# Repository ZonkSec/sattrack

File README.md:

# SatTrack
DIY Satellite Tracker for Ham Radio
* For [Arrow II Sat Antenna](https://www.arrowantennas.com/arrowii/146-437.html)
* improved 3D printed parts | [original design by jbyrns](https://www.thingiverse.com/thing:4664558)
* Nema 17 Motors
* on-board tracking software and battery
  * doubles as a counter weight; fewer wires to get tangled 
  * rasperby pi zero
  * custom pcb for:
    * A4988 Stepper Drivers
    * Power regulation
    * Buzzer output
    * Easy connectivity for switches and connections
  * full featured web interface
  * satellite definitions compatible with opengd77
 
 ## Repo Structure
 The repo is broken into several categories:
 * [3d models](3d%20models) - this contains all the 3d parts, as well as hardware needed
 * [app](app) - this contains the python application
 * [hardware](hardware) - this contains the custom pcb

Each category contains it's own readme.md with more details.

 ## Images

<div align="center">

</div>

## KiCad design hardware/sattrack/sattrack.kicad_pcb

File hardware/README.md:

# Hardware

## Parts Needed:
* 1x Custom PCB
* 1x Raspberry Pi Zero W 1 or 2 (other RPis may work, but these are the only I've tested)
* 2x A4988 Stepper Drivers
* 2x "3d pritner" motor wires (depends on your motor, but mine was the standard 4pin XH 2.54 <-> 6pin PH 2.0)
* 2x Nema 17 Stepper Motors
* 1x 100 µF capacitor (C1)
* 1x 330 µF capacitor (C2)
* 1x 1N5819 Diode (D1)
* 1x 330 µH inductor (L1)
* 1x LM2575 5v switching reg (U1)
* 1x Passive Buzzer (BZ1)
* 2x Mini Toggle Switches ([Link](https://www.amazon.com/dp/B0799LBFNY?))
* 3x JST-XH 2.5pitch 2pin parts for motor enable switch, on/off switch, EL endspot microswitch
* 2x JST-XH 2.5pitch 4pin parts for motor connectors
* 1x Micro Limit Switch KW12-3 for EL limit switch
* 1x Battery connector and wires (I used XT60)
* 1x LiPo Battery ([Link to what I use](https://www.amazon.com/gp/product/B0D59XCQ3Z))
* 1x Roll of 1/2in Hook & Loop Straps to strap battery on
* 1x RC Battery Alarm to monitor voltage

<div align="center">

</div>

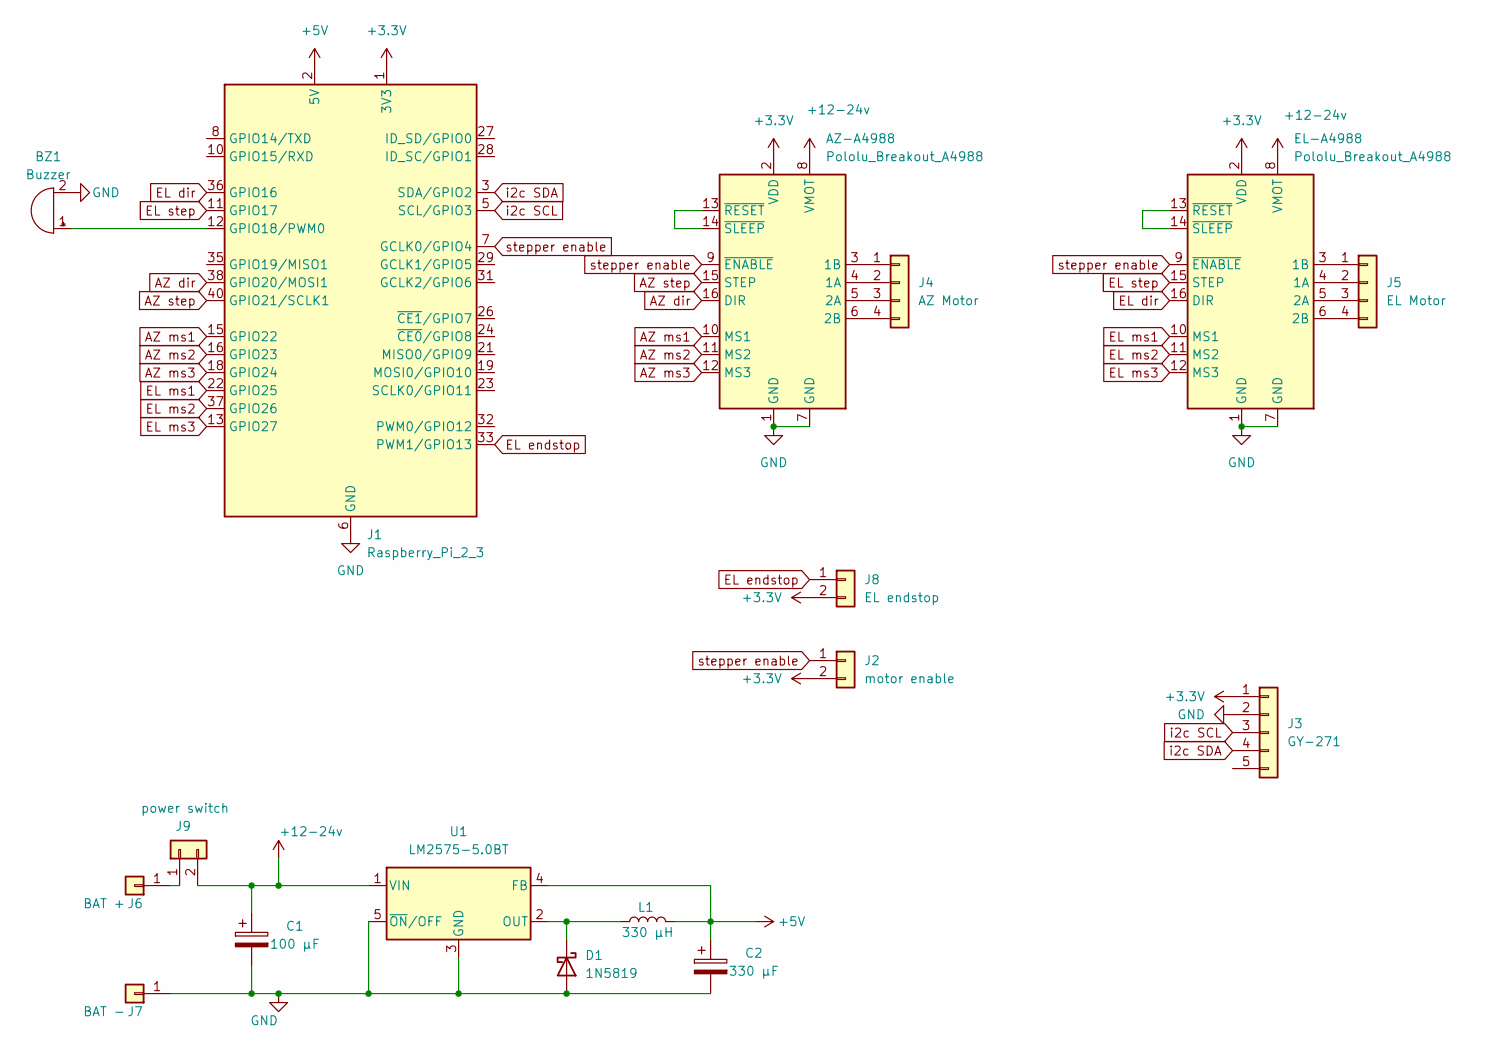
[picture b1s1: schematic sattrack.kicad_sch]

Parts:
AZ-A4988: Pololu_Breakout_A4988; Pololu_Breakout-16_15.2x20.3mm
BZ1: Buzzer; Buzzer_12x9.5RM7.6
C1: 100 µF; CP_Radial_D5.0mm_P2.50mm
C2: 330 µF; CP_Radial_D8.0mm_P3.80mm
D1: 1N5819; D_DO-41_SOD81_P10.16mm_Horizontal
EL-A4988: Pololu_Breakout_A4988; Pololu_Breakout-16_15.2x20.3mm
J1: Raspberry_Pi_2_3; PinHeader_2x20_P2.54mm_Vertical
J2: motor enable; JST_XH_B2B-XH-AM_1x02_P2.50mm_Vertical
J3: GY-271; PinHeader_1x05_P2.54mm_Vertical
J4: AZ Motor; JST_XH_B4B-XH-AM_1x04_P2.50mm_Vertical
J5: EL Motor; JST_XH_B4B-XH-AM_1x04_P2.50mm_Vertical
J6: BAT +; SolderWirePad_1x01_SMD_5x10mm
J7: BAT -; SolderWirePad_1x01_SMD_5x10mm
J8: EL endstop; JST_XH_B2B-XH-AM_1x02_P2.50mm_Vertical
J9: power switch; JST_XH_B2B-XH-AM_1x02_P2.50mm_Vertical
L1: 330 µH; L_Radial_D6.0mm_P4.00mm
U1: LM2575-5.0BT; TO-220-5_Vertical

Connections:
+3.3V: AZ-A4988.2 (VDD), EL-A4988.2 (VDD), J1.1 (3V3), J1.17 (3V3), J2.2, J3.1, J8.2
+5V: C2.1, J1.2 (5V), J1.4 (5V), L1.2, U1.4 (FB)
+12-24v: AZ-A4988.8 (VMOT), C1.1, EL-A4988.8 (VMOT), J9.2, U1.1 (VIN)
AZ dir: AZ-A4988.16 (DIR), J1.38 (GPIO20/MOSI1)
AZ ms1: AZ-A4988.10 (MS1), J1.15 (GPIO22)
AZ ms2: AZ-A4988.11 (MS2), J1.16 (GPIO23)
AZ ms3: AZ-A4988.12 (MS3), J1.18 (GPIO24)
AZ step: AZ-A4988.15 (STEP), J1.40 (GPIO21/SCLK1)
EL dir: EL-A4988.16 (DIR), J1.36 (GPIO16)
EL endstop: J1.33 (PWM1/GPIO13), J8.1
EL ms1: EL-A4988.10 (MS1), J1.22 (GPIO25)
EL ms2: EL-A4988.11 (MS2), J1.37 (GPIO26)
EL ms3: EL-A4988.12 (MS3), J1.13 (GPIO27)
EL step: EL-A4988.15 (STEP), J1.11 (GPIO17)
GND: AZ-A4988.1 (GND), AZ-A4988.7 (GND), BZ1.2 (-), C1.2, C2.2, D1.2 (A), EL-A4988.1 (GND), EL-A4988.7 (GND), J1.6 (GND), J1.9 (GND), J1.14 (GND), J1.20 (GND), J1.25 (GND), J1.30 (GND), J1.34 (GND), J1.39 (GND), J3.2, J7.1, U1.3 (GND), U1.5 (~ON/OFF)
unnamed: AZ-A4988.4 (1A), J4.2
unnamed: AZ-A4988.3 (1B), J4.1
unnamed: AZ-A4988.5 (2A), J4.3
unnamed: AZ-A4988.6 (2B), J4.4
unnamed: AZ-A4988.13 (~RESET), AZ-A4988.14 (~SLEEP)
unnamed: BZ1.1 (+), J1.12 (GPIO18/PWM0)
unnamed: D1.1 (K), L1.1, U1.2 (OUT)
unnamed: EL-A4988.4 (1A), J5.2
unnamed: EL-A4988.3 (1B), J5.1
unnamed: EL-A4988.5 (2A), J5.3
unnamed: EL-A4988.6 (2B), J5.4
unnamed: EL-A4988.13 (~RESET), EL-A4988.14 (~SLEEP)
unnamed: J6.1, J9.1
i2c SCL: J1.5 (SCL/GPIO3), J3.3
i2c SDA: J1.3 (SDA/GPIO2), J3.4
stepper enable: AZ-A4988.9 (~ENABLE), EL-A4988.9 (~ENABLE), J1.7 (GCLK0/GPIO4), J2.1

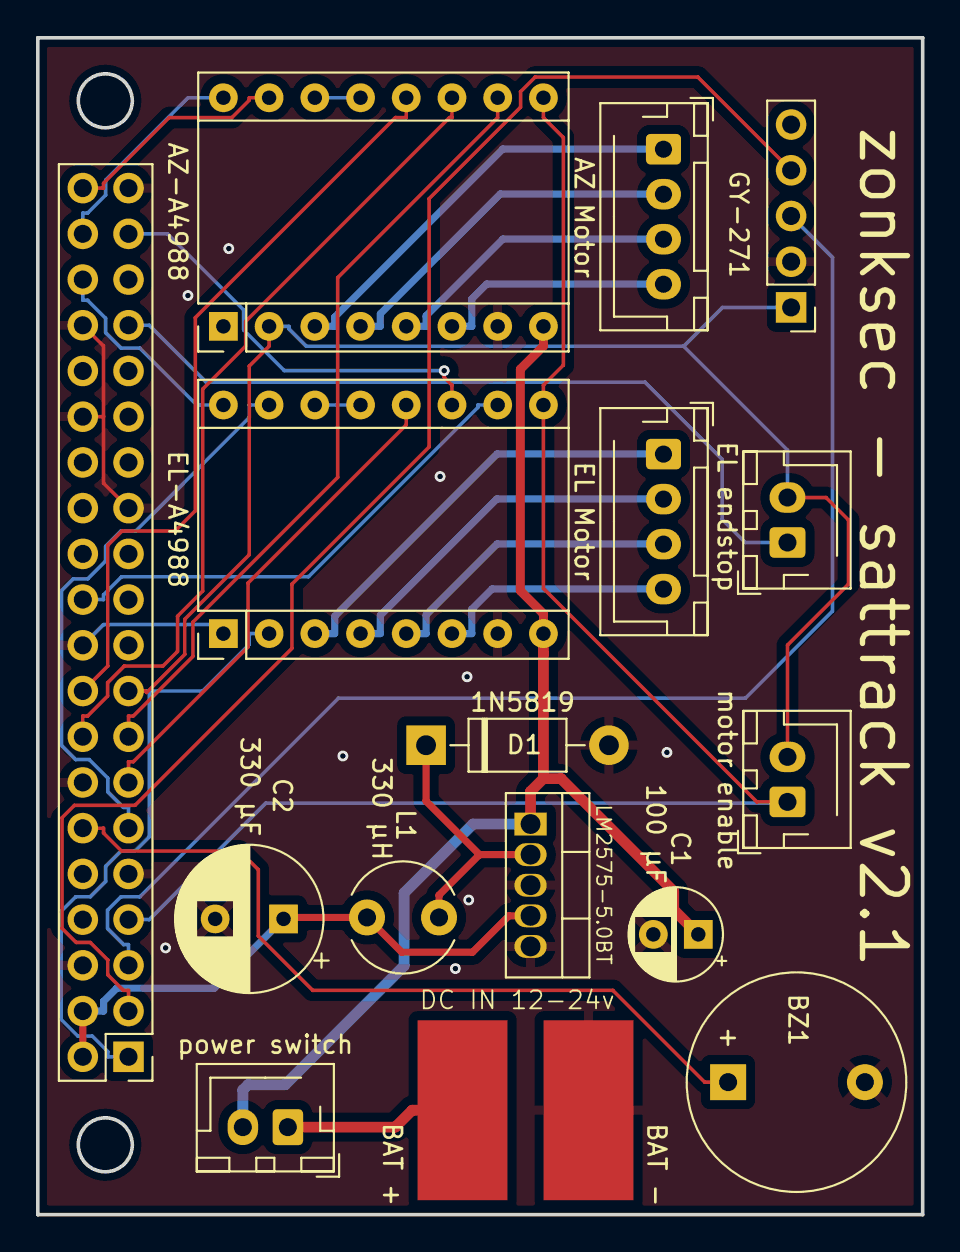
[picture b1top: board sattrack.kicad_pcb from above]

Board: 2 copper layers, 49.2 x 65.4 mm, 17 parts (0 on the bottom side), 31 nets.

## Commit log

2025-01-29 init commit
2025-01-29 adding images
2025-01-29 improved UI buttons. fixed bug in moveTo func
2025-01-29 added manual move protections
    wont manually move if an existing manual if is going
2025-01-29 smoothed out Az movement. fixed a moveTo->tracker EL bug,
2025-01-30 adding a4988 current limit mode script
2025-02-03 motion system tuning
2025-02-04 slowed AZ motor for smoother running. updated TLEs
2025-02-04 add 3d models
2025-02-07 move log to within app. allow it to be viewed via app
2025-02-07 added web app screenshots
2025-02-07 added software photos
2025-02-07 updating pcb files
2025-02-07 adding pcb image and schem
2025-02-07 adding electronic images
2025-02-07 rotate img
2025-02-07 remove pdf schem. add png one
